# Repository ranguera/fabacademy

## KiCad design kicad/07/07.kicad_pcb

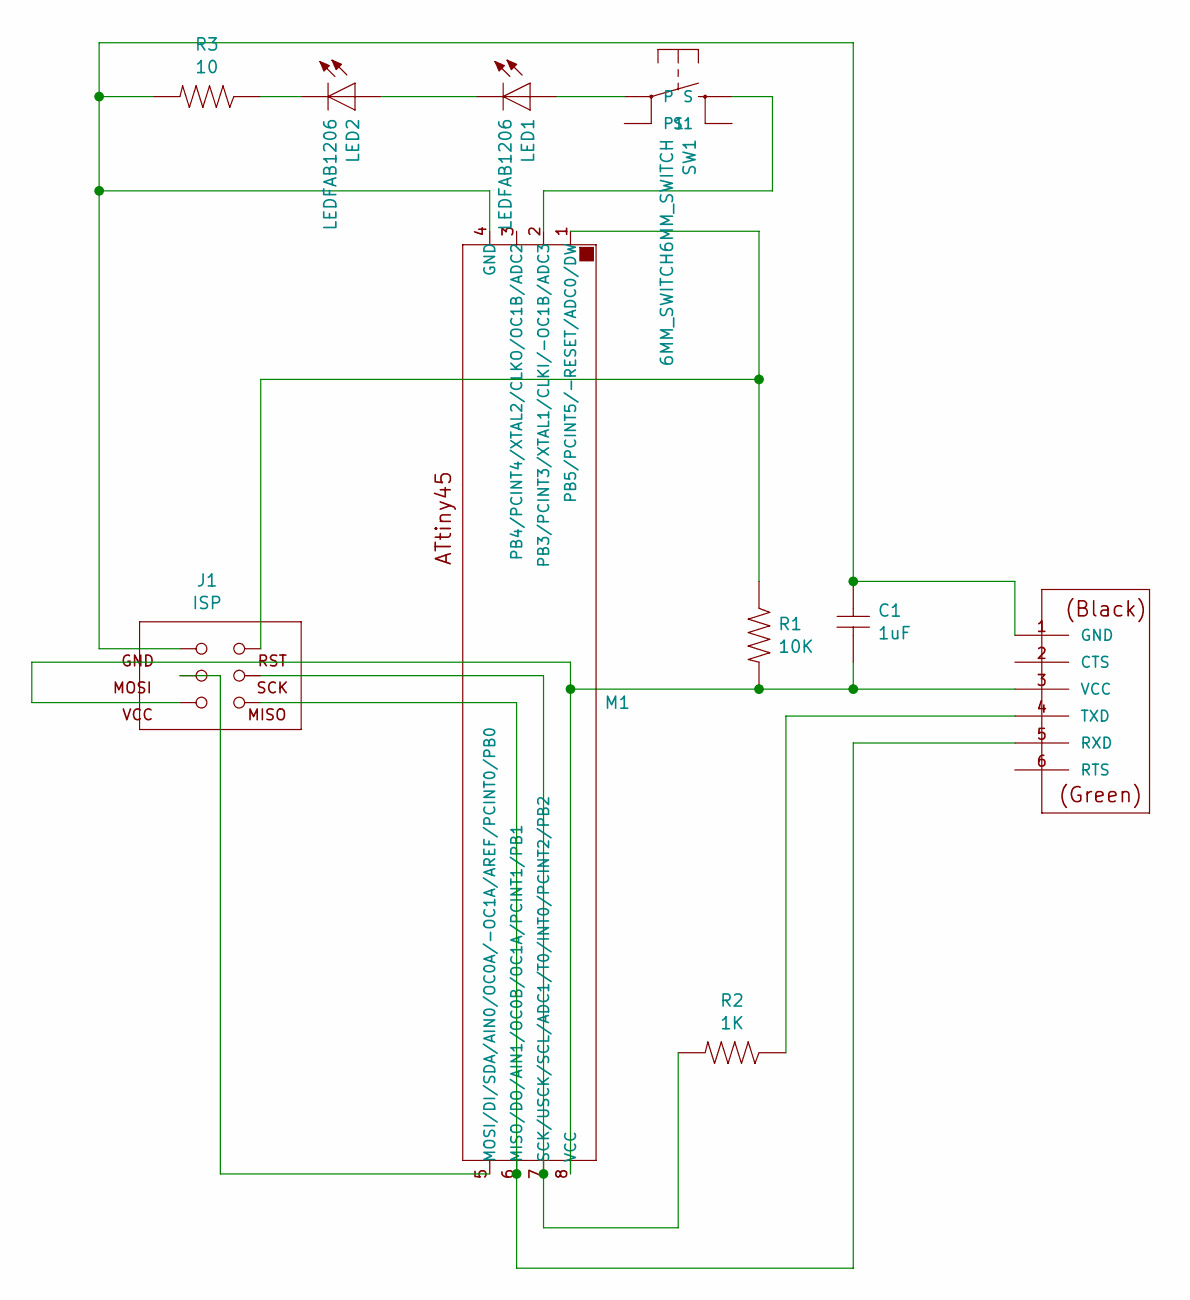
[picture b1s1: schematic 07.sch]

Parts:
C1: 1uF; fab-C1206
FTDI1: FTDI-SMD-HEADER; fab-1X06SMD
J1: ISP; fab-2X03
LED1, LED2: LEDFAB1206; fab-LED1206FAB
M1: ATTINY45SI; fab-SOIC8
R1: 10K; fab-R1206
R2: 1K; fab-R1206
R3: 10; fab-R1206
SW1: 6MM_SWITCH6MM_SWITCH; fab-6MM_SWITCH

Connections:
unnamed 0: C1.1, FTDI1.1 (GND), J1.6 (GND), M1.4 (GND), R3.2; also elsewhere on the board
unnamed 1: C1.2, FTDI1.3 (VCC), J1.2 (VCC), M1.8 (VCC), R1.2; also elsewhere on the board
unnamed: FTDI1.4 (TXD), R2.1
unnamed 4: FTDI1.5 (RXD), J1.1 (MISO), M1.6 (MISO/DO/AIN1/OC0B/OC1A/PCINT1/PB1); also elsewhere on the board
unnamed: LED1.1 (A), SW1.1
unnamed: LED1.2 (C), LED2.1 (A)
unnamed: LED2.2 (C), R3.1
unnamed 9: J1.5 (RST), M1.1 (PB5/PCINT5/-RESET/ADC0/DW), R1.1; also elsewhere on the board
unnamed: M1.2 (PB3/PCINT3/XTAL1/CLKI/-OC1B/ADC3), SW1.3 (S)
unnamed 12: J1.4 (MOSI), M1.5 (MOSI/DI/SDA/AIN0/OC0A/-OC1A/AREF/PCINT0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); also elsewhere on the board
unnamed 13: J1.3 (SCK), M1.7 (SCK/USCK/SCL/ADC1/T0/INT0/PCINT2/PB2), R2.2; also elsewhere on the board

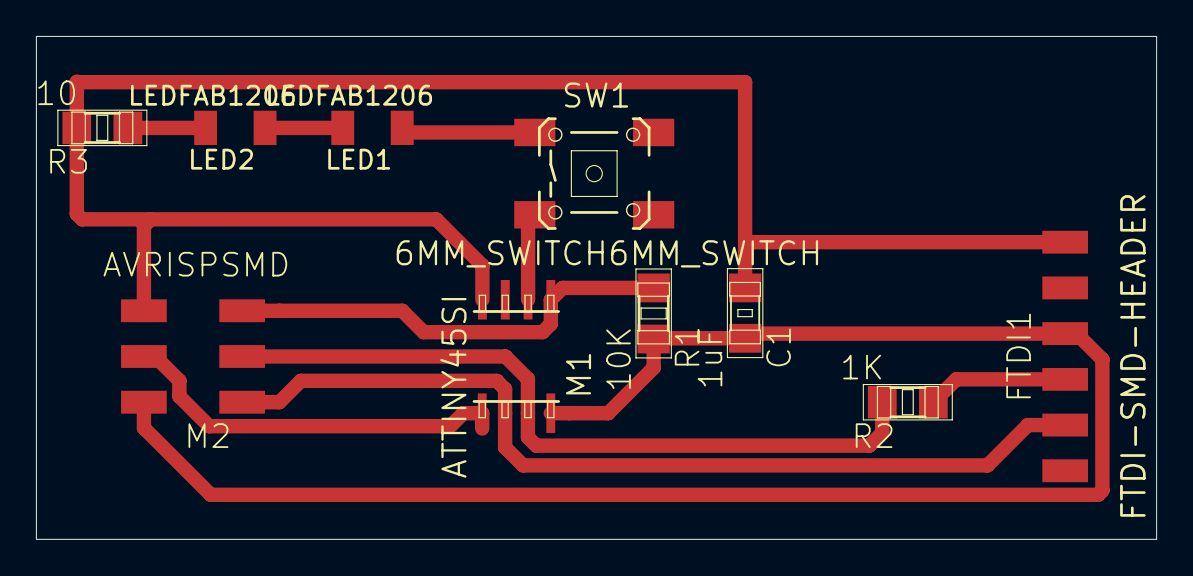
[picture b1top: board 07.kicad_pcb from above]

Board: 2 copper layers, 62.2 x 27.9 mm, 10 parts (0 on the bottom side), 11 nets.

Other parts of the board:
M2: AVRISPSMD; fab-2X03SMD

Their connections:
unnamed 0: M2.6; also elsewhere on the board
unnamed 1: M2.2; also elsewhere on the board
unnamed 4: M2.1; also elsewhere on the board
unnamed 9: M2.5; also elsewhere on the board
unnamed 12: M2.4; also elsewhere on the board
unnamed 13: M2.3; also elsewhere on the board

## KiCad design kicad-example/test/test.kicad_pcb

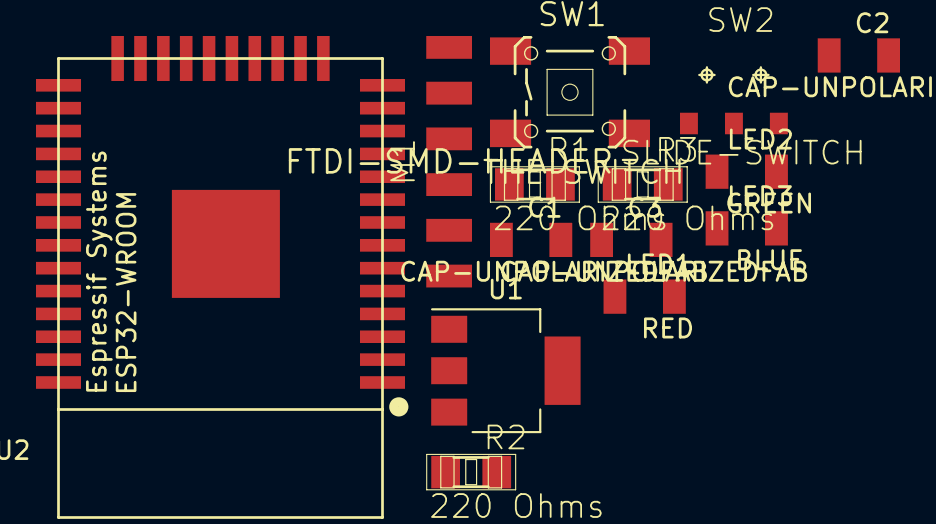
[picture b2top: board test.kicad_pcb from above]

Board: 2 copper layers, 14 parts (0 on the bottom side), 4 nets, no tracks yet.

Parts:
C1, C2, C3: CAP-UNPOLARIZEDFAB; fab-C1206FAB
LED1: RED; fab-LED1206FAB
LED2: GREEN; fab-LED1206FAB
LED3: BLUE; fab-LED1206FAB
M1: FTDI-SMD-HEADER; fab-1X06SMD
R1, R2, R3: 220 Ohms; fab-R1206
SW1: THE SWITCH; fab-6MM_SWITCH
SW2: SLIDE-SWITCH; fab-AYZ0102AGRLC
U1: LT1129-3.3_SOT223; SOT-223-3_TabPin2
U2: ESP32-WROOM; ESP32-WROOM_FAB

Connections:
3V3: C3.2, LED3.2, U1.3, U2.2
GND: C3.1, M1.1, R3.2, U1.2, U2.1
unnamed: LED3.1, R3.1
unnamed: M1.3, U1.1

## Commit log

2020-02-06 rhino and grasshopper
2020-02-06 class notes
2020-02-09 blender class
2020-02-09 illustrator stuff
2020-02-12 cutting class
2020-02-14 cutting class thursday
2020-02-16 hummingbird
2020-02-19 new files
2020-02-20 eletronics and thursday class + milling doc
2020-02-22 feb 20s classes
2020-02-24 rajola2
2020-02-24 nova rajola
2020-02-24 psilo
2020-02-24 electronics-production
2020-02-24 robots class
2020-02-25 trotec tips
2020-02-26 new psilos
2020-02-27 3dprinting
2020-02-28 classes divendres and 3dprinting1
2020-02-29 posavasos
2020-03-02 blender for 3d prniting
2020-03-03 tweaks to illustrators
2020-03-04 electronics design class
2020-03-05 kicad class
2020-03-07 psilo good
2020-03-08 font
2020-03-09 \7 kicad
2020-03-10 good ones
2020-03-11 elephant
2020-03-12 cnc thursday class
2020-03-19 2020-3-18 class notes
2020-03-20 embedded xx
2020-04-16 classe outputs
